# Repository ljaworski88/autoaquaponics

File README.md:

##Welcome to my Automated Aquaponics porject

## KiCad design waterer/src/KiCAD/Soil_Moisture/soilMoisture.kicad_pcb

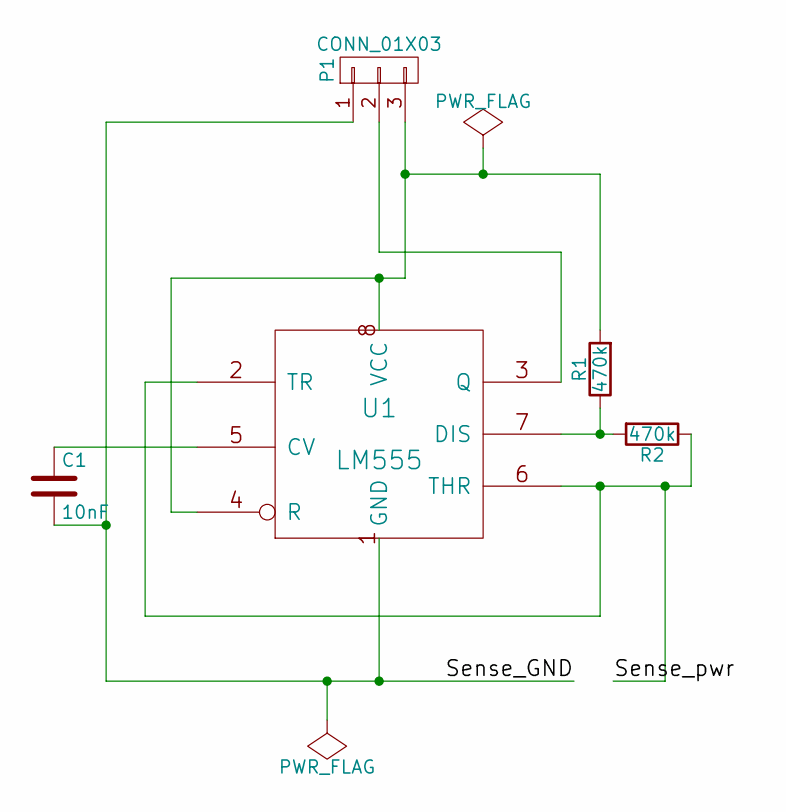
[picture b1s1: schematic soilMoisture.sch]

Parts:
C1: 10nF; C_Disc_D3_P2.5
P1: CONN_01X03; Pin_Header_Straight_1x03
R1, R2: 470k; Resistor_Horizontal_RM7mm
U1: LM555; DIP-8_W7.62mm

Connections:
/Sense_GND: C1.2, P1.1, U1.1 (GND)
/Sense_pwr: R2.1, U1.2 (TR), U1.6 (THR)
unnamed: C1.1, U1.5 (CV)
unnamed: P1.2, U1.3 (Q)
unnamed: P1.3, R1.2, U1.4 (R), U1.8 (VCC)
unnamed: R1.1, R2.2, U1.7 (DIS)

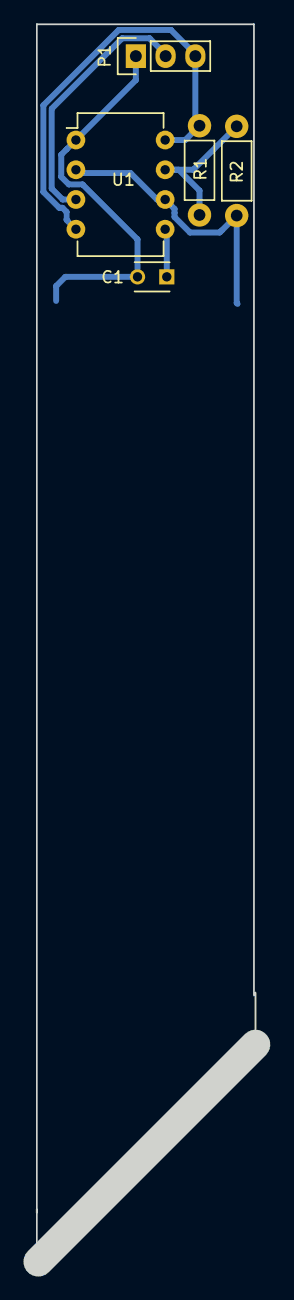
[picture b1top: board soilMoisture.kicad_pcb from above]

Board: 2 copper layers, 18.7 x 105.8 mm, 5 parts (0 on the bottom side), 6 nets.

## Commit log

2019-01-21 initial commit with a bunch of work done,\nSeveral systemd service routines have been written and done
2021-02-15 merged the soil moisture sensor and fixed some api interations as the api of certain libraries changed
2021-02-23 new commit after long break, reformatted file structure and added soil moisture project into codebase
2021-02-23 Add LICENSE
2021-02-23 Add README.md
2022-01-17 merged with autowater project and commited after long absence
2022-01-17 noticed a file that should not have been in the repo
